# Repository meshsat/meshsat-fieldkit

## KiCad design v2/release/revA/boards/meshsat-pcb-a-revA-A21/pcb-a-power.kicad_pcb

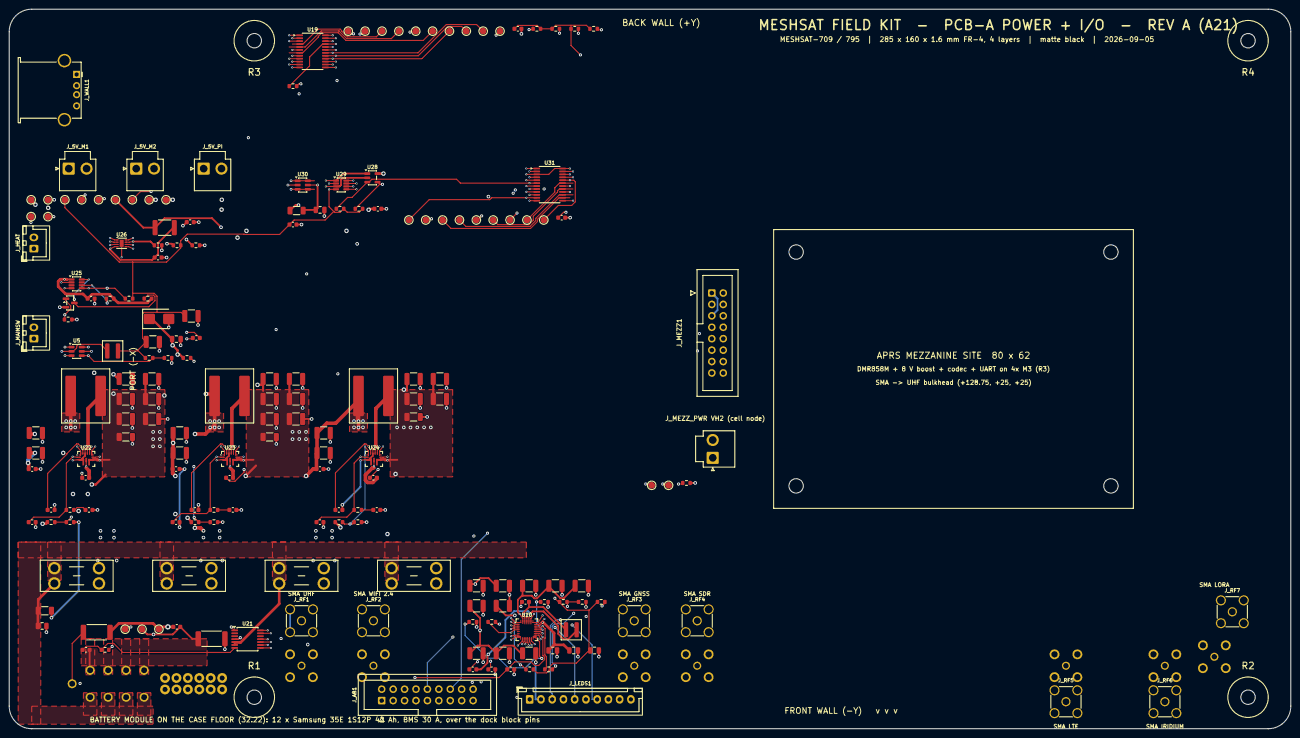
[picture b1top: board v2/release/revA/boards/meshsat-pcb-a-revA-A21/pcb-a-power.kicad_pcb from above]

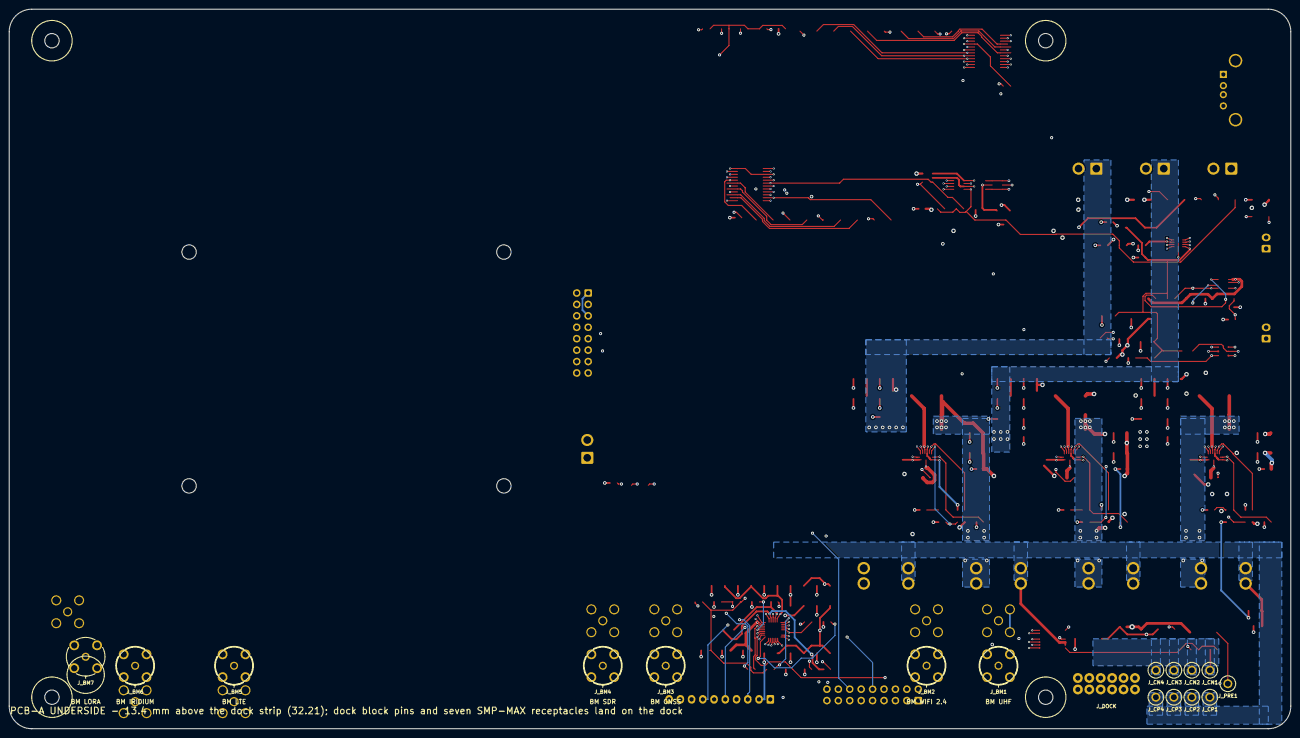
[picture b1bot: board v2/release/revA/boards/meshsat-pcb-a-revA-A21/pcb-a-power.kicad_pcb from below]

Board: 4 copper layers, 285.0 x 160.0 mm, 214 parts (17 on the bottom side), 117 nets.

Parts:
C7, C14, C61, C62, C106: 10u; C_0805_2012Metric
C13, C44, C67, C68, C77, C90, C100, C104, C105, C107, C108: 100n; C_0603_1608Metric
C15, C42, C43, C45, C46, C47, C48, C49, C70, C75, C76, C78, C79, C80, C81, C82, C83, C88, C89, C91, C92, C93, C94, C101: 22u 10V X7R 1210; C_1210_3225Metric
C38, C71, C84: 100n 25V; C_0603_1608Metric
C39, C72, C85: 2.2u; C_0603_1608Metric
C40, C73, C86: 3.3n; C_0603_1608Metric
C41, C74, C87: 27p; C_0603_1608Metric
C50, C95, C96, C97: 100u 10V; C_1206_3216Metric
C51, C52, C53, C54, C55, C56, C57, C58, C59, C60: 10u 25V 1210; C_1210_3225Metric
C63, C64: 47n; C_0603_1608Metric
C65: 4.7u; C_0805_2012Metric
C66: 1n; C_0603_1608Metric
C69, C98: 1u; C_0603_1608Metric
C99: 10n; C_0603_1608Metric
D2: SMBJ5.0A; D_SMB
F2, F3, F4: 10 A mini blade (Keystone 3568 holder): pack node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; Fuseholder_Blade_Mini_Keystone_3568
F5: 15 A mini blade (Keystone 3568 holder): pack node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; Fuseholder_Blade_Mini_Keystone_3568
F6: 2.5A hold 30V 1812; Fuse_1812_4532Metric
H1: M3 rod R1; MountingHole_3.2mm_M3
H2: M3 rod R2; MountingHole_3.2mm_M3
H3: M3 rod R3; MountingHole_3.2mm_M3
H4: M3 rod R4; MountingHole_3.2mm_M3
H5, H6, H7, H8: M3 standoff, mezzanine; MountingHole_3.2mm_M3
J_5V_M1: rail M1 to PCB-B J_5V_M1 (JST-VH, 18 AWG): + -; JST_VH_B2P-VH_1x02_P3.96mm_Vertical
J_5V_M2: rail M2 to PCB-B J_5V_M2 (JST-VH, 18 AWG): + -; JST_VH_B2P-VH_1x02_P3.96mm_Vertical
J_5V_PI: Pi rail 5.1 V 5 A to PCB-B J_5V_PI (JST-VH, 18 AW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; JST_VH_B2P-VH_1x02_P3.96mm_Vertical
J_AB1: A-B interconnect (IDC 2x9, top side); IDC-Header_2x09_P2.54mm_Vertical
J_BM1, J_BM2, J_BM3, J_BM4, J_BM5, J_BM6, J_BM7: SMP-MAX slide-on receptacle R222M00720 (underside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; Radiall_SMPMAX_R222M00720
J_CN1, J_CN2, J_CN3, J_CN4: 9 A spring pin, module return CELL_N (Mill-Max 08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; Mill-Max_0858_power_pin
J_CP1, J_CP2, J_CP3, J_CP4: 9 A spring pin, CELL+ (Mill-Max 0858 class, dock 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; Mill-Max_0858_power_pin
J_DOCK: spring pins to the dock block (2x6, Preci-Dip 813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; PogoPins_2x6
J_HEAT: 12 V heating pad on the battery module (XH2.5): +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; JST_XH_B2B-XH-A_1x02_P2.50mm_Vertical
J_LEDS1: front-wall LED row (XH2.5): PWR MESH SAT LTE SYS; JST_XH_B10B-XH-A_1x10_P2.50mm_Vertical
J_MAINSW: MAIN button lead from the panel (XH2.5): PB, GND; JST_XH_B2B-XH-A_1x02_P2.50mm_Vertical
J_MEZZ1: APRS mezzanine harness (IDC 2x8): I2S and I2C for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; IDC-Header_2x08_P2.54mm_Vertical
J_MEZZ_PWR1: mezzanine 8 V boost feed (JST-VH): cell node thro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; JST_VH_B2P-VH_1x02_P3.96mm_Vertical
J_PRE1: pre-charge pin, longer, mates first (32.24 AX); Mill-Max_0858_power_pin
J_RF1, J_RF2, J_RF3, J_RF4, J_RF5, J_RF6, J_RF7: SMA jack (Amphenol 132134, vertical), pigtail fro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; SMA_Amphenol_132134-11_Vertical
J_WALL1: USB-A receptacle, internal cable to the Glenair 2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; USB_A_Stewart_SS-52100-001_Horizontal
L2, L3, L4: 2.2uH XAL1010-222MED (Isat 34 A, 10 mm); L_Coilcraft_XAL1010-XXX
L5: 2.2uH XAL4030-222MEB (Isat 7.4 A) between SW1 and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; L_Coilcraft_XAL4030-XXX
L6: 3.3uH XAL4020-332MEB; L_Coilcraft_XAL4020-XXX
Q5: 2N7002: Pi GPIO high = pull KILL low = power off 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; SOT-23
R18: 1k; R_0603_1608Metric
R34, R59, R60, R72, R76: 10k; R_0603_1608Metric
R35, R36, R37, R38: 330R; R_0603_1608Metric
R39, R58, R67, R68, R69, R70, R73, R77: 100k; R_0603_1608Metric
R44, R61, R64: 8.87k; R_0603_1608Metric
R47, R62: 102k 1%; R_0603_1608Metric
R48, R63: 13.7k 1%; R_0603_1608Metric
R51: 10R 2W 2512; R_2512_6332Metric
R52: 3 mOhm 1% 3 W 2512 shunt (RALEC LR2512-23R003F4):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; R_2512_6332Metric
R53: 4.7k 1% (PROG: 1S, 750 kHz); R_0603_1608Metric
R54: 16.5k 1%; R_0603_1608Metric
R55: 34.8k 1%; R_0603_1608Metric
R56: 5.23k 1% (RT1 JEITA); R_0603_1608Metric
R57: 30.1k 1% (RT2 JEITA); R_0603_1608Metric
R65: 75k 1%; R_0603_1608Metric
R66, R75: 10k 1%; R_0603_1608Metric
R71: 1.02k 1% (2.0 A); R_0603_1608Metric
R74: 33.2k 1%; R_0603_1608Metric
R78: 0.1R 1% 1206; R_1206_3216Metric
RT1: 10k NTC 0603 1% (gauge temperature, beside the do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; R_0603_1608Metric
TP1: +5V_M1; TestPoint_Pad_D1.5mm
TP2: GND; TestPoint_Pad_D1.5mm
TP3: +3V3; TestPoint_Pad_D1.5mm
TP4: CELL_N; TestPoint_Pad_D1.5mm
TP5: CELL+; TestPoint_Pad_D1.5mm
TP6: SHORE_INHIBIT; TestPoint_Pad_D1.5mm
TP7: GAUGE_ALERT; TestPoint_Pad_D1.5mm
TP8: I2S_DIN; TestPoint_Pad_D1.5mm
TP9: TX_INHIBIT_n; TestPoint_Pad_D1.5mm
TP10: SHORE_12V; TestPoint_Pad_D1.5mm
TP11: CHG_INT; TestPoint_Pad_D1.5mm
TP12: +5V_M2; TestPoint_Pad_D1.5mm
TP13: +5V_PI; TestPoint_Pad_D1.5mm
TP14: DOCK_SPARE; TestPoint_Pad_D1.5mm
TP15: BOOST_EN; TestPoint_Pad_D1.5mm
TP16: CELL_SENSE_P; TestPoint_Pad_D1.5mm
TP17: EXP_SP2; TestPoint_Pad_D1.5mm
TP18: EXP_SP3; TestPoint_Pad_D1.5mm
TP19: EXP2_SP0; TestPoint_Pad_D1.5mm
TP20: EXP2_SP1; TestPoint_Pad_D1.5mm
TP21: EXP2_SP2; TestPoint_Pad_D1.5mm
TP22: EXP2_SP3; TestPoint_Pad_D1.5mm
TP23: EXP2_SP4; TestPoint_Pad_D1.5mm
TP24: EXP2_SP5; TestPoint_Pad_D1.5mm
TP25: EXP2_SP6; TestPoint_Pad_D1.5mm
TP26: EXP2_SP7; TestPoint_Pad_D1.5mm
TP27: EXP2_SP8; TestPoint_Pad_D1.5mm
TP29: EXP_SP4; TestPoint_Pad_D1.5mm
TP30: EXP_SP5; TestPoint_Pad_D1.5mm
TP31: EXP_SP6; TestPoint_Pad_D1.5mm
TP32: EXP_SP7; TestPoint_Pad_D1.5mm
TP33: EXP_SP8; TestPoint_Pad_D1.5mm
TP34: EXP_SP9; TestPoint_Pad_D1.5mm
TP35: EXP_SP10; TestPoint_Pad_D1.5mm
TP36: EXP_SP11; TestPoint_Pad_D1.5mm
U5: TPS563201 3.3 V buck from M1; SOT-23-6
U19: PCA9555PW (0x21); TSSOP-24_4.4x7.8mm_P0.65mm
U20: BQ25792 1S charger from SHORE_12V (3 A set over I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; Texas_RQM0029A_QFN-29_4x4mm
U21: BQ34Z100-G1 gauge (I2C 0x55, SCALED for 42 Ah, 3 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; TSSOP-14_4.4x5mm_P0.65mm
U22: TPS61288L boost +5V_M1 (15 A switch, 500 kHz, no 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; Texas_RQQ0011A_VQFN-HR-11_2.5x3mm
U23: TPS61288L boost +5V_M2 (15 A switch, 500 kHz, no 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; Texas_RQQ0011A_VQFN-HR-11_2.5x3mm
U24: TPS61288L boost +5V_PI (15 A switch, 500 kHz, no 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; Texas_RQQ0011A_VQFN-HR-11_2.5x3mm
U25: LTC2954CTS8-1 push-button on/off controller; TSOT-23-8
U26: TPS259571DSGR eFuse 12 V 2.0 A for the heating pad; Texas_DSG0008A_WSON-8-1EP_2x2mm_P0.5mm_EP0.9x1.6mm
U28: TPS2065CDBV; SOT-23-5
U29: INA219AIDCN; SOT-23-8
U30: USBLC6-2SC6; SOT-23-6
U31: PCA9555PW (0x24): wall port, heating pad, charger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; TSSOP-24_4.4x7.8mm_P0.65mm

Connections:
+3V3: C15.1, C101.1, C105.1, C107.1, C108.1, J_MEZZ1.12, L6.2, R34.2, R35.1, R36.1, R37.1, R38.1, R60.2, R68.2, R72.2, R74.1, R76.2, R77.2, TP3.1, U19.21, U19.24, U29.4, U31.3, U31.24
/5V_WALL: C106.1, J_WALL1.1, R78.2, U29.2, U30.5
/+3V3_AB: J_AB1.17, J_MEZZ1.2
/+5V_M1: C14.1, C45.1, C46.1, C47.1, C48.1, C49.1, C70.1, C95.1, C104.1, D2.1, J_5V_M1.1, R18.1, R47.1, TP1.1, U5.3, U5.5, U22.5, U28.5
/+5V_M2: C78.1, C79.1, C80.1, C81.1, C82.1, C83.1, C96.1, J_5V_M2.1, R62.1, TP12.1, U23.5
/+5V_PI: C91.1, C92.1, C93.1, C94.1, C97.1, J_5V_PI.1, R65.1, TP13.1, U24.5
/BOOST1_IN: C42.1, C43.1, C44.1, F3.2, L2.1, U22.7
/BOOST2_IN: C75.1, C76.1, C77.1, F4.2, L3.1, U23.7
/BOOST3_IN: C88.1, C89.1, C90.1, F5.2, L4.1, U24.7
/BOOST_EN: R67.1, TP15.1, U22.6, U23.6, U24.6, U25.6
/BST1: C38.1, U22.8
/BST2: C71.1, U23.8
/BST3: C84.1, U24.8
/BST33: C13.1, U5.6
/BTST1: C63.1, U20.4
/BTST2: C64.1, U20.19
/CELL+: C7.1, C50.1, C61.1, C62.1, C68.1, C98.1, F2.1, F3.1, F4.1, F5.1, J_CP1.1, J_CP2.1, J_CP3.1, J_CP4.1, R51.2, R67.2, R69.2, TP5.1, U20.22, U20.23, U21.5, U21.6, U25.1
/CELL_N: C68.2, C69.2, J_CN1.1, J_CN2.1, J_CN3.1, J_CN4.1, R52.1, TP4.1, U21.8, U21.9
/CELL_SENSE_P: C67.1, J_DOCK.11, TP16.1, U20.18, U21.4
/CHG_INT: R60.1, TP11.1, U20.21, U31.8
/CHG_STAT: R59.1, U20.1, U31.10
/COMP1: C41.1, R44.1, U22.2
/COMP1C: C40.1, R44.2
/COMP2: C74.1, R61.1, U23.2
/COMP2C: C73.1, R61.2
/COMP3: C87.1, R64.1, U24.2
/COMP3C: C86.1, R64.2
/DOCK_SPARE: J_DOCK.12, TP14.1
/EN_WALL: R77.1, U28.4, U31.4
/EXP2_SP0: TP19.1, U31.11
/EXP2_SP1: TP20.1, U31.13
/EXP2_SP2: TP21.1, U31.14
/EXP2_SP3: TP22.1, U31.15
/EXP2_SP4: TP23.1, U31.16
/EXP2_SP5: TP24.1, U31.17
/EXP2_SP6: TP25.1, U31.18
/EXP2_SP7: TP26.1, U31.19
/EXP2_SP8: TP27.1, U31.20
/EXP_INT: J_AB1.9, R34.1, U19.1, U31.1
/EXP_SP2: TP17.1, U19.9
/EXP_SP3: TP18.1, U19.20
/EXP_SP4: TP29.1, U19.4
/EXP_SP5: TP30.1, U19.5
/EXP_SP6: TP31.1, U19.6
/EXP_SP7: TP32.1, U19.7
/EXP_SP8: TP33.1, U19.16
/EXP_SP9: TP34.1, U19.17
/EXP_SP10: TP35.1, U19.18
/EXP_SP11: TP36.1, U19.19
/FB1: R47.2, R48.1, U22.1
/FB2: R62.2, R63.1, U23.1
/FB3: R65.2, R66.1, U24.1
/FB33: R74.2, R75.1, U5.4
/FLT_WALL: R76.1, U28.3, U31.6
/GAUGE_ALERT: TP7.1, U21.1, U31.9
/HEAT_DVDT: C99.1, U26.1
/HEAT_EN: R73.1, U26.2, U31.5
/HEAT_FLT: R72.1, U26.6, U31.7
/HEAT_ILM: R71.1, U26.7
/HEAT_IN: C100.1, F6.2, U26.3, U26.4
/HEAT_OUT: J_HEAT.1, U26.5
/I2S_BCLK: J_AB1.11, J_MEZZ1.3
/I2S_DIN: J_AB1.16, J_MEZZ1.7, TP8.1
/I2S_DOUT: J_AB1.15, J_MEZZ1.6
/I2S_LRCLK: J_AB1.12, J_MEZZ1.4
/ILIM_HIZ: R54.2, R55.1, U20.17
/KILL: Q5.3, R69.1, U25.8
/LED_LTE_A: J_LEDS1.7, R37.2
/LED_LTE_K: J_LEDS1.8, U19.14
/LED_MESH_A: J_LEDS1.3, R35.2
/LED_MESH_K: J_LEDS1.4, U19.11
/LED_PWR_A: J_LEDS1.1, R18.2
/LED_SAT_A: J_LEDS1.5, R36.2
/LED_SAT_K: J_LEDS1.6, U19.13
/LED_SYS_A: J_LEDS1.9, R38.2
/LED_SYS_K: J_LEDS1.10, U19.15
/MAIN_PB: J_MAINSW.1, U25.2
/MEZZ_CELL: F2.2, J_MEZZ_PWR1.1
/MEZZ_EN: J_MEZZ1.11, U19.10
/PI_KILL: J_AB1.2, Q5.1, R70.1
/PI_SHDN_REQ: J_AB1.1, R68.1, U25.5
/PMID: C53.1, C54.1, C55.1, U20.29
/PRECHG: J_PRE1.1, R51.1
/PROG: R53.1, U20.20
/QON: R58.2, U20.12
/REG25: C69.1, RT1.1, U21.7
/REGN: C65.1, R54.1, R56.1, R58.1, R59.2, U20.5
/RF_IRIDIUM: J_BM6.1, J_RF6.1
/RF_LORA: J_BM7.1, J_RF7.1
/RF_LTE: J_BM5.1, J_RF5.1
/RF_SDR: J_BM4.1, J_RF4.1
/RF_UHF: J_BM1.1, J_RF1.1
/RF_WIFI24: J_BM2.1, J_RF2.1
/RF_WIFI58: J_BM3.1, J_RF3.1
/SCL: J_AB1.8, J_MEZZ1.14, U19.22, U20.14, U21.13, U29.5, U31.22
/SDA: J_AB1.7, J_MEZZ1.9, U19.23, U20.15, U21.14, U29.6, U29.7, U29.8, U31.23
/SDRV: C66.1, U20.24
/SHORE_12V: C51.1, C52.1, F6.1, J_DOCK.1, J_DOCK.2, J_DOCK.3, J_DOCK.4, TP10.1, U20.2, U20.3, U20.8, U20.9
/SHORE_INHIBIT: J_DOCK.8, TP6.1, U19.8
/SW1: C38.2, L2.2, U22.4, U22.9
/SW1_CHG: C63.2, L5.1, U20.28
/SW2: C71.2, L3.2, U23.4, U23.9
/SW2_CHG: C64.2, L5.2, U20.26
/SW3: C84.2, L4.2, U24.4, U24.9
/SW33: C13.2, L6.1, U5.2
/SW_WALL: R78.1, U28.1, U29.1
/SYS_CHG: C56.1, C57.1, C58.1, C59.1, C60.1, U20.25
/TR_APRS: J_AB1.10, J_MEZZ1.10, R39.1
/TS_CHG: J_DOCK.9, R56.2, R57.1, U20.16
/TS_GAUGE: RT1.2, U21.11
/TX_INHIBIT_n: J_AB1.14, J_MEZZ1.15, TP9.1
/USB_WALL_N: J_AB1.5, J_WALL1.2, U30.3, U30.4
/USB_WALL_P: J_AB1.4, J_WALL1.3, U30.1, U30.6
/VCC1: C39.1, U22.11
/VCC2: C72.1, U23.11
/VCC3: C85.1, U24.11
GND: C7.2, C14.2, C15.2, C39.2, C40.2, C41.2, C42.2, C43.2, C44.2, C45.2, C46.2, C47.2, C48.2, C49.2, C50.2, C51.2, C52.2, C53.2, C54.2, C55.2, C56.2, C57.2, C58.2, C59.2, C60.2, C61.2, C62.2, C65.2, C66.2, C67.2, C70.2, C72.2, C73.2, C74.2, C75.2, C76.2, C77.2, C78.2, C79.2, C80.2, C81.2, C82.2, C83.2, C85.2, C86.2, C87.2, C88.2, C89.2, C90.2, C91.2, C92.2, C93.2, C94.2, C95.2, C96.2, C97.2, C98.2, C99.2, C100.2, C101.2, C104.2, C105.2, C106.2, C107.2, C108.2, D2.2, J_5V_M1.2, J_5V_M2.2, J_5V_PI.2, J_AB1.3, J_AB1.6, J_AB1.13, J_AB1.18, J_BM1.2, J_BM2.2, J_BM3.2, J_BM4.2, J_BM5.2, J_BM6.2, J_BM7.2, J_DOCK.5, J_DOCK.6, J_DOCK.7, J_DOCK.10, J_HEAT.2, J_LEDS1.2, J_MAINSW.2, J_MEZZ1.1, J_MEZZ1.5, J_MEZZ1.8, J_MEZZ1.13, J_MEZZ1.16, J_MEZZ_PWR1.2, J_RF1.2, J_RF2.2, J_RF3.2, J_RF4.2, J_RF5.2, J_RF6.2, J_RF7.2, J_WALL1.4, J_WALL1.5, Q5.2, R39.2, R48.2, R52.2, R53.2, R55.2, R57.2, R63.2, R66.2, R70.2, R71.2, R73.2, R75.2, TP2.1, U5.1, U19.2, U19.3, U19.12, U20.10, U20.11, U20.13, U20.27, U21.10, U22.3, U22.10, U23.3, U23.10, U24.3, U24.10, U25.4, U26.8, U26.9, U28.2, U29.3, U30.2, U31.2, U31.12, U31.21

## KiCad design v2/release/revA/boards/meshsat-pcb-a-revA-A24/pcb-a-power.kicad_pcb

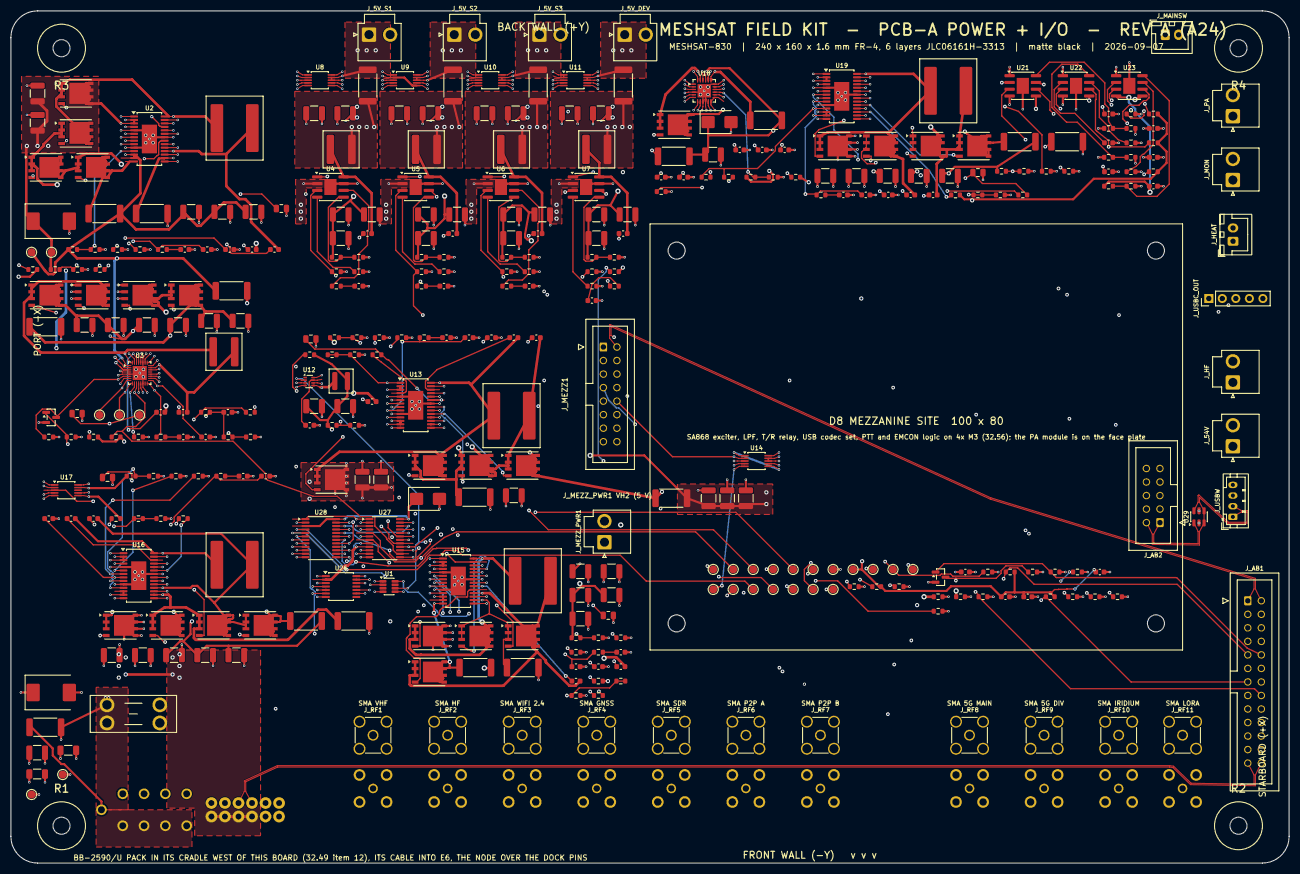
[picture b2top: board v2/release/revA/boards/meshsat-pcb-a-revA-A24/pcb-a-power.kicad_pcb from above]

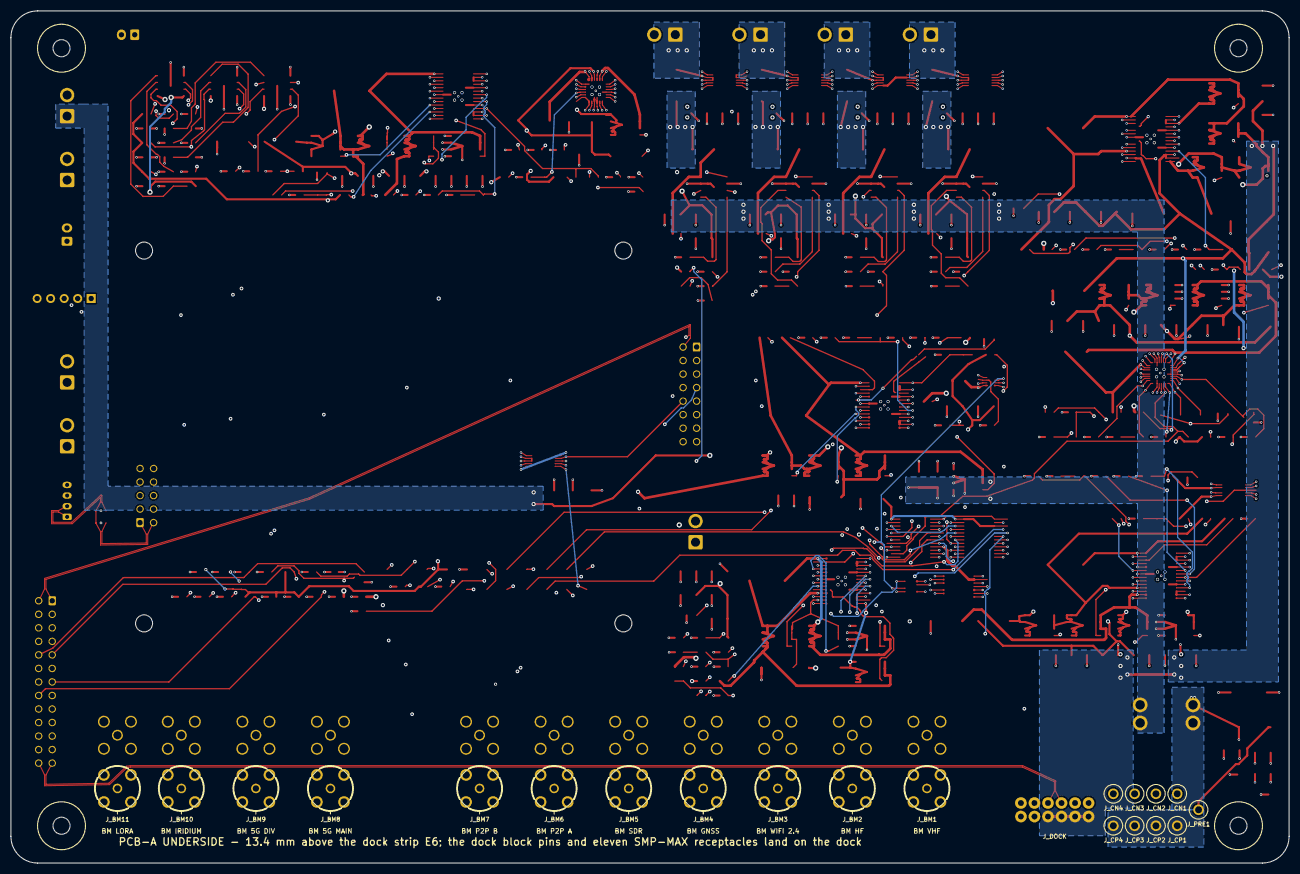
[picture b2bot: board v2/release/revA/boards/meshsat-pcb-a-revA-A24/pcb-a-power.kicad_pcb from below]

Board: 6 copper layers, 240.0 x 160.0 mm, 400 parts (21 on the bottom side), 250 nets.

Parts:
C1, C2: 47u 25V; C_1206_3216Metric
C3, C29, C30, C35, C36, C41, C42, C47, C48, C54, C120: 10u 25V 1210; C_1210_3225Metric
C4, C19: 1u; C_0603_1608Metric
C5, C26, C53, C57, C68, C75, C86, C98, C100, C102: 10n; C_0603_1608Metric
C6, C58, C69, C76, C87: 100p; C_0603_1608Metric
C7, C59, C70, C77, C88: 47n; C_0603_1608Metric
C8, C60, C71, C78, C89: 4.7u; C_0805_2012Metric
C9, C10, C16, C17, C61, C62, C72, C73, C79, C80, C90, C91: 100n 25V; C_0603_1608Metric
C11, C12, C13, C14, C15, C63, C64, C65, C66, C67, C74, C81, C82, C92, C108, C109, C110, C111, C116, C117, C118, C119: 10u 50V X7R 1210; C_1210_3225Metric
C18: 3.3u; C_0805_2012Metric
C20, C21, C22: 10u 35V 1210; C_1210_3225Metric
C23, C24, C25: 22u 25V 1210; C_1210_3225Metric
C27: 1n; C_0603_1608Metric
C28, C34, C40, C46, C52, C93, C95, C99, C101, C103, C104, C106, C107: 100n; C_0603_1608Metric
C31, C32, C33, C37, C38, C39, C43, C44, C45, C49, C50, C51, C55, C56: 22u 10V X7R 1210; C_1210_3225Metric
C83, C84, C85: 10u 100V X7R 1210; C_1210_3225Metric
C94: 220n; C_0603_1608Metric
C96, C97: 330p; C_0603_1608Metric
C112, C113, C114, C115: 3.3n; C_0603_1608Metric
D1: SMCJ18A (VBAT clamp); D_SMC
D2: SMCJ33A (VIN_RAW clamp behind E6's filter); D_SMC
D3: SMBJ5.0A; D_SMB
D4: SMBJ18A (VBUS clamp at the outlet); D_SMB
F1: 25 A mini blade (Keystone 3568 holder): pack node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; Fuseholder_Blade_Mini_Keystone_3568
H1: M3 rod R1; MountingHole_3.2mm_M3
H2: M3 rod R2; MountingHole_3.2mm_M3
H3: M3 rod R3; MountingHole_3.2mm_M3
H4: M3 rod R4; MountingHole_3.2mm_M3
H5, H6, H7, H8: M3 standoff, mezzanine; MountingHole_3.2mm_M3
J_5V_DEV: USB device rail to B16 (JST-VH): + -; JST_VH_B2P-VH_1x02_P3.96mm_Vertical
J_5V_S1: slot 1 5.1 V rail to B16 (JST-VH, 16 AWG): + -; JST_VH_B2P-VH_1x02_P3.96mm_Vertical
J_5V_S2: slot 2 5.1 V rail to B16 (JST-VH, 16 AWG): + -; JST_VH_B2P-VH_1x02_P3.96mm_Vertical
J_5V_S3: slot 3 5.1 V rail to B16 (JST-VH, 16 AWG): + -; JST_VH_B2P-VH_1x02_P3.96mm_Vertical
J_54V: 54 V to the PoE injector on B16 (JST-VH): + -; JST_VH_B2P-VH_1x02_P3.96mm_Vertical
J_AB1: A-B interconnect (IDC 2x13, top side) to B16's un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; IDC-Header_2x13_P2.54mm_Vertical_NarrowPad
J_AB2: A-B wall-port ribbon (IDC 2x5): the wall USB pair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; IDC-Header_2x05_P2.54mm_Vertical_NarrowPad
J_BM1, J_BM2, J_BM3, J_BM4, J_BM5, J_BM6, J_BM7, J_BM8, J_BM9, J_BM10, J_BM11: SMP-MAX slide-on receptacle R222M00720 (underside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; Radiall_SMPMAX_R222M00720
J_CN1, J_CN2, J_CN3, J_CN4: 9 A spring pin, pack return (Mill-Max 0858 class,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; Mill-Max_0858_power_pin
J_CP1, J_CP2, J_CP3, J_CP4: 9 A spring pin, CELL+ (Mill-Max 0858 class, dock 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; Mill-Max_0858_power_pin
J_DOCK: spring pins to the dock block (2x6, Preci-Dip 813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; PogoPins_2x6
J_HEAT: JST-XH 1x2 socket: the heater mat under the 2590 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; JST_XH_B2B-XH-A_1x02_P2.50mm_Vertical
J_HF: 12.0 V to the QMX HF unit in its lid tray (JST-VH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; JST_VH_B2P-VH_1x02_P3.96mm_Vertical
J_MAINSW: JST-XH 1x2 socket: the MAIN button lead from the 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; JST_XH_B2B-XH-A_1x02_P2.50mm_Vertical
J_MEZZ1: D8 mezzanine harness (IDC 2x8): its USB pair, the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; IDC-Header_2x08_P2.54mm_Vertical_NarrowPad
J_MEZZ_PWR1: D8 mezzanine 5 V (JST-VH): + -; JST_VH_B2P-VH_1x02_P3.96mm_Vertical
J_MON: monitor supply lead to the Xenarc (JST-VH): + -; JST_VH_B2P-VH_1x02_P3.96mm_Vertical
J_PA: 13.8 V to the PA module on the face plate (JST-VH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; JST_VH_B2P-VH_1x02_P3.96mm_Vertical
J_PRE1: pre-charge pin, longer, mates first (32.24 AX); Mill-Max_0858_power_pin
J_RF1, J_RF2, J_RF3, J_RF4, J_RF5, J_RF6, J_RF7, J_RF8, J_RF9, J_RF10, J_RF11: SMA jack (Amphenol 132134, vertical), pigtail fro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; SMA_Amphenol_132134-11_Vertical
J_USBC_OUT: wall USB-C outlet, power side (pigtail header): V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; PinHeader_1x05_P2.54mm_Vertical
J_USBW: JST-PH 1x4 socket: the wall USB-C data pair to B1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; JST_PH_B4B-PH-K_1x04_P2.00mm_Vertical
L1: 10uH XAL1010-103ME (Isat 14 A); L_Coilcraft_XAL1010-XXX
L2: 3.3uH XAL6030-332ME (Isat 12.2 A); L_Coilcraft_XAL6060-XXX
L3, L4, L5, L6: 4.7uH XAL6060-472ME (Isat 11 A); L_Coilcraft_XAL6060-XXX
L7: 4.7uH XAL4030-472ME; L_Coilcraft_XAL4030-XXX
L8: 6.8uH XAL1010-682ME (Isat 17 A); L_Coilcraft_XAL1010-XXX
L9, L11: 6.8uH XAL1010-682ME; L_Coilcraft_XAL1010-XXX
L10: 22uH XAL1010-223ME (Isat 9 A); L_Coilcraft_XAL1010-XXX
Q1: 2N7002: panel controller high = pull KILL low = p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; SOT-23
Q2, Q3, Q4, Q5, Q17, Q18, Q19, Q20: CSD19532Q5B 100 V N-FET (4.6 mOhm at VGS 6 V, Pow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; PowerPAK_SO-8_Single
Q6: 2N7002: CHG_INHIBIT high = ILIM_HIZ low = charger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; SOT-23
Q7, Q8, Q9, Q10, Q11, Q12, Q13, Q14, Q15, Q16, Q21, Q22, Q23, Q24, Q25, Q26: CSD18510Q5B 40 V N-FET; PowerPAK_SO-8_Single
Q27: CSD18510Q5B 40 V N-FET (VBUS switch); PowerPAK_SO-8_Single
R1: 10R 2W 2512; R_2512_6332Metric
R2, R3, R4, R5, R13, R21, R30, R34, R38, R42, R57, R73, R102, R103, R104, R111, R112, R113, R114, R116, R118, R123, R128, R143, R145: 100k; R_0603_1608Metric
R6: 240k 1%; R_0603_1608Metric
R7, R15, R29, R33, R37, R41, R49, R51, R59, R61, R67, R75, R125, R134: 10k 1%; R_0603_1608Metric
R8, R52, R62, R68, R78: 40.2k (300 kHz); R_0603_1608Metric
R9, R53, R63, R69, R79: 30k (slope); R_0603_1608Metric
R10, R22, R23, R25, R44, R54, R64, R70, R80, R91, R95, R99, R110, R117, R142: 10k; R_0603_1608Metric
R11, R65, R81, R138: 10mOhm 1% 2512 (ISNS); R_2512_6332Metric
R12, R56, R122, R127: 5mOhm 1% 2512 (CS); R_2512_6332Metric
R14, R58, R74, R124, R133: 62k 1%; R_0603_1608Metric
R16: 10mOhm 1% 2512 (RAC, input current sense); R_2512_6332Metric
R17: 5mOhm 1% 2512 (RSR, charge current sense); R_2512_6332Metric
R18: 10R; R_0603_1608Metric
R19: 16.5k 1%; R_0603_1608Metric
R20: 34.8k 1%; R_0603_1608Metric
R24: 10k (PSYS load); R_0603_1608Metric
R26: 60.4k 1% (CELL_BATPRESZ: 4S per Table, from VDDA); R_0603_1608Metric
R27: 40.2k 1%; R_0603_1608Metric
R28, R32, R36, R40: 53.6k 1%; R_0603_1608Metric
R31, R35, R39, R43: 5mOhm 1% 2512 (shunt); R_2512_6332Metric
R45, R46, R47, R115: 68k (RT: 500 kHz); R_0603_1608Metric
R48: 31.6k 1%; R_0603_1608Metric
R50: 162k 1%; R_0603_1608Metric
R55: 2mOhm 1% 2512 (ISNS); R_2512_6332Metric
R60: 140k 1%; R_0603_1608Metric
R66: 665k 1%; R_0603_1608Metric
R71: 20mOhm 1% 2512 (ISNS); R_2512_6332Metric
R72: 10mOhm 1% 2512 (CS); R_2512_6332Metric
R76: 105k 1%; R_0603_1608Metric
R77: 20k 1% (R_FBL); R_0603_1608Metric
R90: 750R 1% (ILM: 1.2 A); R_0603_1608Metric
R92, R96, R100: 100k 1%; R_0603_1608Metric
R93, R97, R101: 10k 1% (OVLO); R_0603_1608Metric
R94: 909R 1% (ILM: 1.0 A); R_0603_1608Metric
R98: 453R 1% (ILM: 2.0 A); R_0603_1608Metric
R119, R120, R121, R126, R135: 100k (MODE: CCM); R_0603_1608Metric
R129, R130, R131, R132: 22k; R_0603_1608Metric
R136: 21.0k 1% (R_FBL2: 9 V when CTL2 is low); R_0603_1608Metric
R137: 14.0k 1% (R_FBL1: 15 V when CTL1 is low too); R_0603_1608Metric
R139: 43R 1W 2512 (DSCG); R_2512_6332Metric
R140: 1M (GD to VPWR, 9.1.3); R_0603_1608Metric
R141: 698k; R_0603_1608Metric
TP3: EXP2_SP3; TestPoint_Pad_D1.5mm
TP4: EXP2_SP4; TestPoint_Pad_D1.5mm
TP5: EXP2_SP5; TestPoint_Pad_D1.5mm
TP6: EXP2_SP6; TestPoint_Pad_D1.5mm
TP7: EXP2_SP7; TestPoint_Pad_D1.5mm
TP8: EXP2_SP8; TestPoint_Pad_D1.5mm
TP9: VBAT; TestPoint_Pad_D1.5mm
TP10: GND; TestPoint_Pad_D1.5mm
TP11: +3V3; TestPoint_Pad_D1.5mm
TP12: VBUS20; TestPoint_Pad_D1.5mm
TP13: VIN_RAW; TestPoint_Pad_D1.5mm
TP14: CELL+; TestPoint_Pad_D1.5mm
TP15: EMCON_HW; TestPoint_Pad_D1.5mm
TP16: RAIL_EN; TestPoint_Pad_D1.5mm
TP17: SDA; TestPoint_Pad_D1.5mm
TP18: SCL; TestPoint_Pad_D1.5mm
TP19: IADPT; TestPoint_Pad_D1.5mm
TP20: IBAT; TestPoint_Pad_D1.5mm
TP21: DOCK_SPARE; TestPoint_Pad_D1.5mm
TP22: REGN; TestPoint_Pad_D1.5mm
TP23: EXP2_SPA; TestPoint_Pad_D1.5mm
TP24: EXP2_SPB; TestPoint_Pad_D1.5mm
TP25: EXP2_SPC; TestPoint_Pad_D1.5mm
TP26: EXP2_SPD; TestPoint_Pad_D1.5mm
TP27: AB_SPARE; TestPoint_Pad_D1.5mm
U1: LTC2954CTS8-1 push-button on/off controller; TSOT-23-8
U2: LM5176PWPR buck-boost controller, VBUS20 from VIN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; HTSSOP-28-1EP_4.4x9.7mm_P0.65mm_EP2.85x5.4mm
U3: BQ25731RSNR 1 to 5 cell buck-boost charger, 4S fr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; QFN-32-1EP_4x4mm_P0.4mm_EP2.65x2.65mm
U4: AP64500SP-13 5 A buck, 5.1 V rail +5V_S1; SOIC-8-1EP_3.9x4.9mm_P1.27mm_EP2.29x3mm
U5: AP64500SP-13 5 A buck, 5.1 V rail +5V_S2; SOIC-8-1EP_3.9x4.9mm_P1.27mm_EP2.29x3mm
U6: AP64500SP-13 5 A buck, 5.1 V rail +5V_S3; SOIC-8-1EP_3.9x4.9mm_P1.27mm_EP2.29x3mm
U7: AP64500SP-13 5 A buck, 5.1 V rail +5V_DEV; SOIC-8-1EP_3.9x4.9mm_P1.27mm_EP2.29x3mm
U8: INA226 rail monitor +5V_S1; VSSOP-10_3x3mm_P0.5mm
U9: INA226 rail monitor +5V_S2; VSSOP-10_3x3mm_P0.5mm
U10: INA226 rail monitor +5V_S3; VSSOP-10_3x3mm_P0.5mm
U11: INA226 rail monitor +5V_DEV; VSSOP-10_3x3mm_P0.5mm
U12: TPS62933DRLR 3 A buck, 3.3 V logic; SOT-583-8
U13: LM5176PWPR buck-boost controller, +13V8_PA from V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; HTSSOP-28-1EP_4.4x9.7mm_P0.65mm_EP2.85x5.4mm
U14: INA226 PA rail monitor (0x46); VSSOP-10_3x3mm_P0.5mm
U15: LM5176PWPR buck-boost controller, +12V_HF from VB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; HTSSOP-28-1EP_4.4x9.7mm_P0.65mm_EP2.85x5.4mm
U16: LM5176PWPR buck-boost controller, +54V_POE from V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; HTSSOP-28-1EP_4.4x9.7mm_P0.65mm_EP2.85x5.4mm
U17: INA226 PoE rail monitor (0x47); VSSOP-10_3x3mm_P0.5mm
U18: TPS25740ARGER USB-C PD source controller, 45 W ou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; QFN-24-1EP_4x4mm_P0.5mm_EP2.5x2.5mm
U19: LM5176PWPR buck-boost controller, PD_VPWR from VB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; HTSSOP-28-1EP_4.4x9.7mm_P0.65mm_EP2.85x5.4mm
U21: TPS259631DDAR eFuse VBAT -> VMON (750R 1% (ILM: 1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; SOIC-8-1EP_3.9x4.9mm_P1.27mm_EP2.29x3mm
U22: TPS259631DDAR eFuse VBAT -> VHEAT (909R 1% (ILM: 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; SOIC-8-1EP_3.9x4.9mm_P1.27mm_EP2.29x3mm
U23: TPS259631DDAR eFuse +5V_DEV -> +5V_D8 (453R 1% (I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; SOIC-8-1EP_3.9x4.9mm_P1.27mm_EP2.29x3mm
U26: SN74LVC08APWR quad AND: EMCON gates for the PA ra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; TSSOP-14_4.4x5mm_P0.65mm
U27: PCA9555PW (0x21): enables and status; TSSOP-24_4.4x7.8mm_P0.65mm
U28: PCA9555PW (0x24): power-good lines, spares; TSSOP-24_4.4x7.8mm_P0.65mm
U29: USBLC6-2SC6; SOT-23-6

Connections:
+3V3: C55.1, C56.1, C104.1, C106.1, C107.1, D3.1, J_MEZZ1.13, L7.2, R3.2, R13.2, R22.2, R23.2, R44.2, R48.1, R57.2, R73.2, R91.2, R95.2, R99.2, R110.2, R117.2, R123.2, R128.2, R142.2, TP11.1, U8.6, U9.2, U9.6, U10.1, U10.6, U11.1, U11.2, U11.6, U14.1, U14.6, U17.1, U17.6, U26.14, U27.21, U27.24, U28.3, U28.24
/+5V_D8: J_MEZZ_PWR1.1, U23.5
/+5V_DEV: C49.1, C50.1, C51.1, C103.1, J_5V_DEV.1, R40.1, R43.2, R100.1, U11.8, U11.9, U18.17, U23.4, U29.5
/+5V_S1: C31.1, C32.1, C33.1, J_5V_S1.1, R28.1, R31.2, U8.8, U8.9
/+5V_S2: C37.1, C38.1, C39.1, J_5V_S2.1, R32.1, R35.2, U9.8, U9.9
/+5V_S3: C43.1, C44.1, C45.1, J_5V_S3.1, R36.1, R39.2, U10.8, U10.9
/+12V_HF: C109.1, C110.1, C111.1, J_HF.1, R60.1, R65.2, U15.12, U15.13, U15.24
/+13V8_PA: C65.1, C66.1, C67.1, J_PA.1, R50.1, R55.2, U13.12, U13.13, U13.24, U14.8, U14.9
/+54V_POE: C83.1, C84.1, C85.1, J_54V.1, R66.1, R71.2, U16.12, U16.13, U17.9
/AB_SPARE: J_MEZZ1.16, TP27.1
/B33_BST: C52.1, U12.6
/B33_FB: R48.2, R49.1, U12.8
/B33_SS: C53.1, U12.7
/B33_SW: C52.2, L7.1, U12.5
/CELL+: F1.1, J_CP1.1, J_CP2.1, J_CP3.1, J_CP4.1, R1.2, R17.2, TP14.1, U3.19
/CHG_ILIM: Q6.3, R19.2, R20.1, U3.6
/CHG_INHIBIT: Q6.1, R21.1, U27.4
/CHRG_OK: R22.1, U3.4, U27.13
/CH_ACN: C20.1, C21.1, C22.1, Q7.5, R16.2, U3.2
/CH_BTST1: C16.1, U3.30
/CH_BTST2: C17.1, U3.25
/CH_CELL: R26.2, R27.1, U3.18
/CH_COMP1: R25.1, U3.16
/CH_COMP1C: C26.1, R25.2
/CH_COMP2: C27.1, U3.17
/CH_HIDRV1: Q7.4, U3.31
/CH_HIDRV2: Q10.4, U3.24
/CH_LODRV1: Q8.4, U3.29
/CH_LODRV2: Q9.4, U3.26
/CH_SRP: C23.1, C24.1, C25.1, Q10.5, R17.1, U3.20, U3.22
/CH_SW1: C16.2, L2.1, Q7.1, Q7.2, Q7.3, Q8.5, U3.32
/CH_SW2: C17.2, L2.2, Q9.5, Q10.1, Q10.2, Q10.3, U3.23
/CH_VDDA: C19.1, R18.2, R26.1, U3.7
/D8_EN: R113.1, U23.3, U27.7
/D8_FLT: R99.1, U23.6, U27.17
/DEV_EN: R42.1, U7.3, U27.11
/DOCK_SPARE: J_DOCK.12, TP21.1, U27.18
/EMCON_HW: J_AB1.15, R102.1, TP15.1, U26.1, U26.4
/EXP2_SP3: TP3.1, U28.15
/EXP2_SP4: TP4.1, U28.16
/EXP2_SP5: TP5.1, U28.17
/EXP2_SP6: TP6.1, U28.18
/EXP2_SP7: TP7.1, U28.19
/EXP2_SP8: TP8.1, U28.20
/EXP2_SPA: TP23.1, U28.4
/EXP2_SPB: TP24.1, U28.5
/EXP2_SPC: TP25.1, U28.6
/EXP2_SPD: TP26.1, U28.7
/EXP_INT: J_AB1.13, J_MEZZ1.12, R110.1, U27.1, U28.1
/FE_BOOT1: C9.1, U2.26
/FE_BOOT2: C10.1, U2.20
/FE_COMP: C6.1, R10.1, U2.9
/FE_COMPC: C5.1, R10.2
/FE_CS: Q3.1, Q3.2, Q3.3, Q4.1, Q4.2, Q4.3, R12.1, U2.16
/FE_EN: R14.2, R15.1, U2.1
/FE_FB: R6.2, R7.1, U2.11
/FE_HDRV1: Q2.4, U2.27
/FE_HDRV2: Q5.4, U2.19
/FE_LDRV1: Q3.4, U2.25
/FE_LDRV2: Q4.4, U2.21
/FE_MODE: R119.1, U2.4
/FE_OUT: Q5.5, R11.1, U2.14
/FE_PGOOD: R13.1, U2.17, U27.20
/FE_RT: R8.1, U2.6
/FE_SLOPE: R9.1, U2.7
/FE_SS: C7.1, U2.8
/FE_SW1: C9.2, L1.1, Q2.1, Q2.2, Q2.3, Q3.5, U2.28
/FE_SW2: C10.2, L1.2, Q4.5, Q5.1, Q5.2, Q5.3, U2.18
/FE_VCC: C8.1, R119.2, U2.23
/HEAT_EN: R112.1, U22.3, U27.6
/HEAT_FLT: R95.1, U22.6, U27.16
/HF_BOOT1: C72.1, U15.26
/HF_BOOT2: C73.1, U15.20
/HF_COMP: C69.1, R64.1, U15.9
/HF_COMPC: C68.1, R64.2
/HF_CS: Q16.1, Q16.2, Q16.3, Q23.1, Q23.2, Q23.3, R122.1, U15.16
/HF_EN: R124.1, R124.2, R125.1, U15.1, U26.6
/HF_FB: R60.2, R61.1, U15.11
/HF_HDRV1: Q15.4, U15.27
/HF_HDRV2: Q24.4, U15.19
/HF_LDRV1: Q16.4, U15.25
/HF_LDRV2: Q23.4, U15.21
/HF_MODE: R126.1, U15.4
/HF_OUT: Q24.5, R65.1, U15.14
/HF_PGOOD: R123.1, U15.17, U28.10
/HF_RT: R62.1, U15.6
/HF_SLOPE: R63.1, U15.7
/HF_SS: C70.1, U15.8
/HF_SW1: C72.2, L9.1, Q15.1, Q15.2, Q15.3, Q16.5, U15.28
/HF_SW2: C73.2, L9.2, Q23.5, Q24.1, Q24.2, Q24.3, U15.18
/HF_SW_EN: R104.1, U26.5, U27.10
/HF_VCC: C71.1, R126.2, U15.23
/IADPT: TP19.1, U3.8
/IBAT: TP20.1, U3.9
/INA_ALERT: R44.1, U8.3, U9.3, U10.3, U11.3, U14.3, U17.3, U27.19
/KILL: Q1.3, R4.1, U1.8
/MAIN_PB: J_MAINSW.1, U1.2
/MON_EN: R111.1, U21.3, U27.5
/MON_FLT: R91.1, U21.6, U27.15
/PA_BOOT1: C61.1, U13.26
/PA_BOOT2: C62.1, U13.20
/PA_COMP: C58.1, R54.1, U13.9
/PA_COMPC: C57.1, R54.2
/PA_CS: Q12.1, Q12.2, Q12.3, Q13.1, Q13.2, Q13.3, R56.1, U13.16
/PA_EN: J_MEZZ1.9, R58.1, R58.2, R59.1, U13.1, U26.3
/PA_FB: R50.2, R51.1, U13.11
/PA_HDRV1: Q11.4, U13.27
/PA_HDRV2: Q14.4, U13.19
/PA_LDRV1: Q12.4, U13.25
/PA_LDRV2: Q13.4, U13.21
/PA_MODE: R120.1, U13.4
/PA_OUT: Q14.5, R55.1, U13.14, U14.10
/PA_PGOOD: R57.1, U13.17, U28.8
/PA_RT: R52.1, U13.6
/PA_SLOPE: R53.1, U13.7
/PA_SS: C59.1, U13.8
/PA_SW1: C61.2, L8.1, Q11.1, Q11.2, Q11.3, Q12.5, U13.28
/PA_SW2: C62.2, L8.2, Q13.5, Q14.1, Q14.2, Q14.3, U13.18
/PA_SW_EN: R103.1, U26.2, U27.9
/PA_VCC: C60.1, R120.2, U13.23
/PD_BOOT1: C90.1, U19.26
/PD_BOOT2: C91.1, U19.20
/PD_CC1: C96.1, J_USBC_OUT.2, U18.2
/PD_CC2: C97.1, J_USBC_OUT.3, U18.3
/PD_COMP: C87.1, R80.1, U19.9
/PD_COMPC: C86.1, R80.2
/PD_CS: Q22.1, Q22.2, Q22.3, Q25.1, Q25.2, Q25.3, R127.1, U19.16
/PD_CTL1: R137.2, U18.6
/PD_CTL2: R136.2, U18.7
/PD_DSCG: R139.1, U18.24
/PD_DVDD: C94.1, U18.5, U18.8, U18.12, U18.13
/PD_EN: R133.1, R133.2, R134.1, R143.1, U19.1, U28.13
/PD_FB: R76.2, R77.1, R136.1, R137.1, U19.11
/PD_GD: R140.2, R141.1, U18.15
/PD_GDNG: Q27.4, U18.22
/PD_HDRV1: Q21.4, U19.27
/PD_HDRV2: Q26.4, U19.19
/PD_LDRV1: Q22.4, U19.25
/PD_LDRV2: Q25.4, U19.21
/PD_MODE: R135.1, U19.4
/PD_OUT: Q26.5, R81.1, U19.14
/PD_PGOOD: R128.1, U19.17, U28.11
/PD_RT: R78.1, U19.6
/PD_SLOPE: R79.1, U19.7
/PD_SS: C88.1, U19.8
/PD_SW: Q27.1, Q27.2, Q27.3, R138.1, U18.19, U18.23
/PD_SW1: C90.2, L11.1, Q21.1, Q21.2, Q21.3, Q22.5, U19.28
/PD_SW2: C91.2, L11.2, Q25.5, Q26.1, Q26.2, Q26.3, U19.18
/PD_UFP: R142.1, U18.11, U28.14
/PD_VAUX: C95.1, U18.14, U18.16
/PD_VBUS: C120.1, D4.1, J_USBC_OUT.1, R138.2, R139.2, U18.21
/PD_VCC: C89.1, R135.2, U19.23
/PD_VPWR: C117.1, C118.1, C119.1, Q27.5, R76.1, R81.2, R140.1, U18.20, U19.12, U19.13, U19.24
/PD_VTX: C93.1, U18.1
/PI_KILL: J_AB1.10, Q1.1, R5.1
/PI_SHDN_REQ: J_AB1.9, R3.1, U1.5
/POE_BOOT1: C79.1, U16.26
/POE_BOOT2: C80.1, U16.20
/POE_COMP: C76.1, R70.1, U16.9
/POE_COMPC: C75.1, R70.2
/POE_CS: Q18.1, Q18.2, Q18.3, Q19.1, Q19.2, Q19.3, R72.1, U16.16
/POE_EN: R74.1, R74.2, R75.1, R114.1, U16.1, U27.8
/POE_FB: R66.2, R67.1, U16.11
/POE_HDRV1: Q17.4, U16.27
/POE_HDRV2: Q20.4, U16.19
/POE_LDRV1: Q18.4, U16.25
/POE_LDRV2: Q19.4, U16.21
/POE_MODE: R121.1, U16.4
/POE_OUT: Q20.5, R71.1, U16.14, U17.10
/POE_PGOOD: R73.1, U16.17, U28.9
/POE_RT: R68.1, U16.6
/POE_SLOPE: R69.1, U16.7
/POE_SS: C77.1, U16.8
/POE_SW1: C79.2, L10.1, Q17.1, Q17.2, Q17.3, Q18.5, U16.28
/POE_SW2: C80.2, L10.2, Q19.5, Q20.1, Q20.2, Q20.3, U16.18
/POE_VCC: C78.1, R121.2, U16.23
/PRECHG: J_PRE1.1, R1.1
/PROCHOT: R23.1, U3.11, U27.14
/PSYS: R24.1, U3.10
/RAIL_EN: R2.1, TP16.1, U1.6, U12.2
/REGN: C18.1, R18.1, R19.1, TP22.1, U3.28
/RF_5G1: J_BM8.1, J_RF8.1
/RF_5G2: J_BM9.1, J_RF9.1
/RF_GNSS: J_BM4.1, J_RF4.1
/RF_HF: J_BM2.1, J_RF2.1
/RF_IRIDIUM: J_BM10.1, J_RF10.1
/RF_LORA: J_BM11.1, J_RF11.1
/RF_P2PA: J_BM6.1, J_RF6.1
/RF_P2PB: J_BM7.1, J_RF7.1
/RF_SDR: J_BM5.1, J_RF5.1
/RF_VHF: J_BM1.1, J_RF1.1
/RF_WIFI24: J_BM3.1, J_RF3.1
/S1_BOOT: C28.1, U4.1
/S1_COMP: R129.1, U4.6
/S1_COMPC: C112.1, R129.2
/S1_FB: R28.2, R29.1, U4.5
/S1_OUT: L3.2, R31.1, U8.10
/S1_RT: R45.1, U4.4
/S1_SW: C28.2, L3.1, U4.8
/S2_BOOT: C34.1, U5.1
/S2_COMP: R130.1, U5.6
/S2_COMPC: C113.1, R130.2
/S2_FB: R32.2, R33.1, U5.5
/S2_OUT: L4.2, R35.1, U9.10
/S2_RT: R46.1, U5.4
/S2_SW: C34.2, L4.1, U5.8
/S3_BOOT: C40.1, U6.1
/S3_COMP: R131.1, U6.6
/S3_COMPC: C114.1, R131.2
/S3_FB: R36.2, R37.1, U6.5
/S3_OUT: L5.2, R39.1, U10.10
/S3_RT: R47.1, U6.4
/S3_SW: C40.2, L5.1, U6.8
/SCL: J_AB1.12, J_MEZZ1.11, TP18.1, U3.13, U8.5, U9.5, U10.5, U11.5, U14.5, U17.2, U17.5, U27.22, U28.22
/SDA: J_AB1.11, J_MEZZ1.10, TP17.1, U3.12, U8.4, U9.4, U10.4, U11.4, U14.2, U14.4, U17.4, U27.23, U28.23
/SD_BOOT: C46.1, U7.1
/SD_COMP: R132.1, U7.6
/SD_COMPC: C115.1, R132.2
/SD_FB: R40.2, R41.1, U7.5
/SD_OUT: L6.2, R43.1, U11.10
/SD_RT: R115.1, U7.4
/SD_SW: C46.2, L6.1, U7.8
/SHORE_INHIBIT: J_AB1.21, J_DOCK.8, R118.1
/SLOT_EN1: J_AB1.17, R30.1, U4.3
/SLOT_EN2: J_AB1.18, R34.1, U5.3
/SLOT_EN3: J_AB1.19, R38.1, U6.3
/TR_APRS: J_AB1.14, J_MEZZ1.7, R116.1
/TX_INHIBIT_n: J_AB1.16, J_MEZZ1.8, R145.1
/U21_DVDT: C98.1, U21.2
/U21_ILM: R90.1, U21.7
/U21_OVLO: R92.2, R93.1, U21.8
/U22_DVDT: C100.1, U22.2
/U22_ILM: R94.1, U22.7
/U22_OVLO: R96.2, R97.1, U22.8
/U23_DVDT: C102.1, U23.2
/U23_ILM: R98.1, U23.7
/U23_OVLO: R100.2, R101.1, U23.8
/USB_D8_N: J_AB1.2, J_MEZZ1.2
/USB_D8_P: J_AB1.1, J_MEZZ1.1
/USB_E6_N: J_AB1.26, J_DOCK.10
/USB_E6_P: J_AB1.25, J_DOCK.9
/USB_WALL_N: J_AB2.2, J_USBW.2, U29.3, U29.4
/USB_WALL_P: J_AB2.1, J_USBW.1, U29.1, U29.6
/VBAT: C1.1, C2.1, C3.1, C4.1, C29.1, C30.1, C35.1, C36.1, C41.1, C42.1, C47.1, C48.1, C54.1, C63.1, C64.1, C74.1, C81.1, C82.1, C92.1, C99.1, C101.1, C108.1, C116.1, D1.1, F1.2, Q11.5, Q15.5, Q17.5, Q21.5, R2.2, R4.2, R92.1, R96.1, TP9.1, U1.1, U4.2, U5.2, U6.2, U7.2, U12.3, U13.2, U13.3, U15.2, U15.3, U16.2, U16.3, U16.24, U19.2, U19.3, U21.4, U22.4
/VBUS20: C13.1, C14.1, C15.1, R6.1, R11.2, R16.1, TP12.1, U2.12, U2.13, U2.24, U3.1, U3.3
/VHEAT: J_HEAT.1, U22.5
/VIN_RAW: C11.1, C12.1, D2.1, J_DOCK.1, J_DOCK.2, J_DOCK.3, J_DOCK.4, Q2.5, R14.1, TP13.1, U2.2, U2.3
/VMON: J_MON.1, U21.5
/ZEROIZE_HW: J_AB1.20, J_MEZZ1.15, R117.1
GND: C1.2, C2.2, C3.2, C4.2, C5.2, C6.2, C7.2, C8.2, C11.2, C12.2, C13.2, C14.2, C15.2, C18.2, C19.2, C20.2, C21.2, C22.2, C23.2, C24.2, C25.2, C26.2, C27.2, C29.2, C30.2, C31.2, C32.2, C33.2, C35.2, C36.2, C37.2, C38.2, C39.2, C41.2, C42.2, C43.2, C44.2, C45.2, C47.2, C48.2, C49.2, C50.2, C51.2, C53.2, C54.2, C55.2, C56.2, C57.2, C58.2, C59.2, C60.2, C63.2, C64.2, C65.2, C66.2, C67.2, C68.2, C69.2, C70.2, C71.2, C74.2, C75.2, C76.2, C77.2, C78.2, C81.2, C82.2, C83.2, C84.2, C85.2, C86.2, C87.2, C88.2, C89.2, C92.2, C93.2, C94.2, C95.2, C96.2, C97.2, C98.2, C99.2, C100.2, C101.2, C102.2, C103.2, C104.2, C106.2, C107.2, C108.2, C109.2, C110.2, C111.2, C112.2, C113.2, C114.2, C115.2, C116.2, C117.2, C118.2, C119.2, C120.2, D1.2, D2.2, D3.2, D4.2, J_5V_DEV.2, J_5V_S1.2, J_5V_S2.2, J_5V_S3.2, J_54V.2, J_AB1.3, J_AB1.4, J_AB1.5, J_AB1.6, J_AB1.7, J_AB1.8, J_AB1.22, J_AB1.23, J_AB1.24, J_AB2.3, J_AB2.4, J_AB2.5, J_AB2.6, J_AB2.7, J_AB2.8, J_AB2.9, J_AB2.10, J_BM1.2, J_BM2.2, J_BM3.2, J_BM4.2, J_BM5.2, J_BM6.2, J_BM7.2, J_BM8.2, J_BM9.2, J_BM10.2, J_BM11.2, J_CN1.1, J_CN2.1, J_CN3.1, J_CN4.1, J_DOCK.5, J_DOCK.6, J_DOCK.7, J_DOCK.11, J_HEAT.2, J_HF.2, J_MAINSW.2, J_MEZZ1.3, J_MEZZ1.4, J_MEZZ1.5, J_MEZZ1.6, J_MEZZ1.14, J_MEZZ_PWR1.2, J_MON.2, J_PA.2, J_RF1.2, J_RF2.2, J_RF3.2, J_RF4.2, J_RF5.2, J_RF6.2, J_RF7.2, J_RF8.2, J_RF9.2, J_RF10.2, J_RF11.2, J_USBC_OUT.4, J_USBC_OUT.5, J_USBW.3, J_USBW.4, Q1.2, Q6.2, Q8.1, Q8.2, Q8.3, Q9.1, Q9.2, Q9.3, R5.2, R7.2, R8.2, R9.2, R12.2, R15.2, R20.2, R21.2, R24.2, R27.2, R29.2, R30.2, R33.2, R34.2, R37.2, R38.2, R41.2, R42.2, R45.2, R46.2, R47.2, R49.2, R51.2, R52.2, R53.2, R56.2, R59.2, R61.2, R62.2, R63.2, R67.2, R68.2, R69.2, R72.2, R75.2, R77.2, R78.2, R79.2, R90.2, R93.2, R94.2, R97.2, R98.2, R101.2, R102.2, R103.2, R104.2, R111.2, R112.2, R113.2, R114.2, R115.2, R116.2, R118.2, R122.2, R125.2, R127.2, R134.2, R141.2, R143.2, R145.2, TP10.1, U1.4, U2.5, U2.10, U2.15, U2.22, U2.29, U3.5, U3.14, U3.27, U3.33, U4.7, U4.9, U5.7, U5.9, U6.7, U6.9, U7.7, U7.9, U8.1, U8.2, U8.7, U9.1, U9.7, U10.2, U10.7, U11.7, U12.4, U13.5, U13.10, U13.15, U13.22, U13.29, U14.7, U15.5, U15.10, U15.15, U15.22, U15.29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

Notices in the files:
v2/release/revA/boards/meshsat-pcb-c-revA-C24/pcb-c-display.kicad_sch:
page 1 of 5 MeshSat field kit V2, CERN-OHL-S-2.0 PROTOTYPE, nothing built 2026-09-16
page 2 of 5 MeshSat field kit V2, CERN-OHL-S-2.0 PROTOTYPE, nothing built 2026-09-16
page 3 of 5 MeshSat field kit V2, CERN-OHL-S-2.0 PROTOTYPE, nothing built 2026-09-16
page 4 of 5 MeshSat field kit V2, CERN-OHL-S-2.0 PROTOTYPE, nothing built 2026-09-16
page 5 of 5 MeshSat field kit V2, CERN-OHL-S-2.0 PROTOTYPE, nothing built 2026-09-16
